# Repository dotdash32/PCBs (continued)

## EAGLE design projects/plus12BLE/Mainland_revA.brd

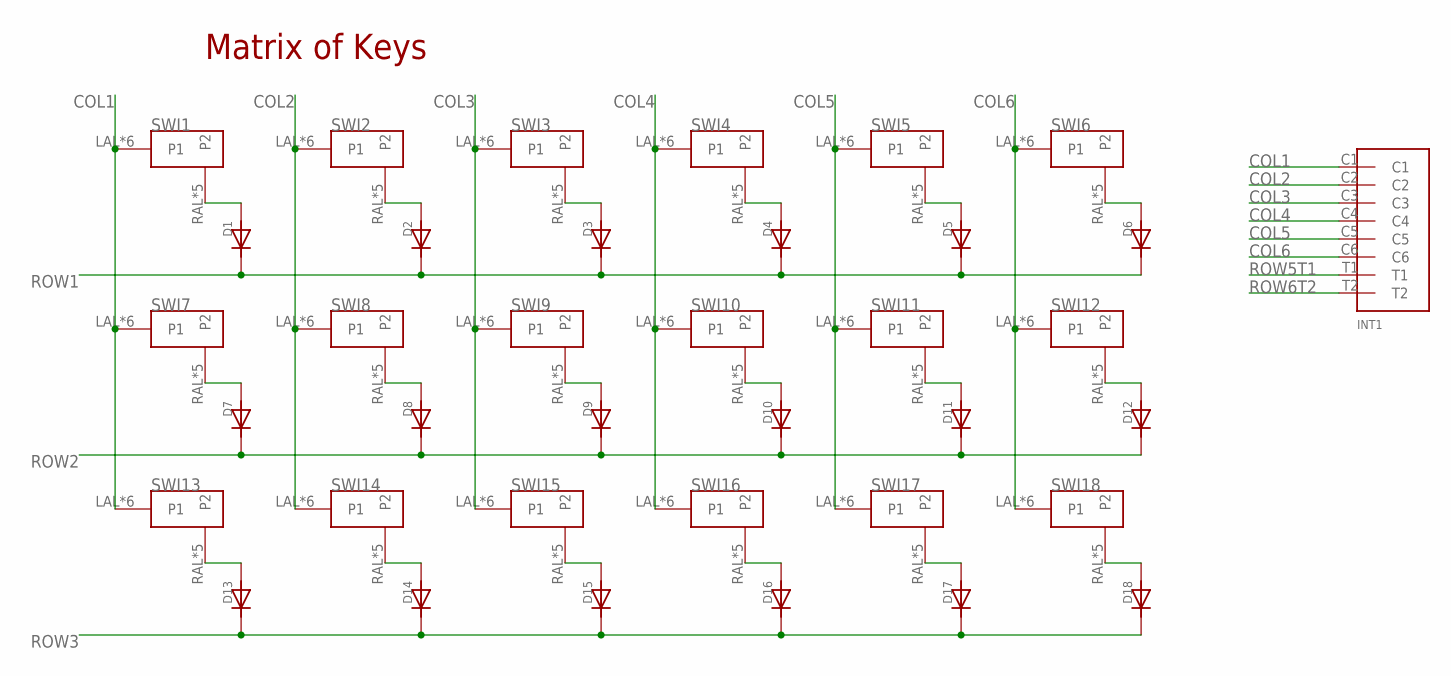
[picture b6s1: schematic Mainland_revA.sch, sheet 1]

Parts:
D1, D2, D3, D4, D5, D6, D7, D8, D9, D10, D11, D12, D13, D14, D15, D16, D17, D18: DIODE; DIODE_COMBO
INT1: INTRCNNT4X2; INTRRIBBON
SWI1, SWI2, SWI3, SWI4, SWI5, SWI6, SWI7, SWI8, SWI9, SWI10, SWI11, SWI12, SWI13, SWI14, SWI15, SWI16, SWI17, SWI18: MX/ALPSDOUBLESIDED; DOUBLED_MX/ALPS

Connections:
COL1: INT1.C1, SWI1.LAL (P1), SWI1.LAR (P1), SWI1.LCL (P1), SWI1.LCR (P1), SWI1.LLP (P1), SWI1.LRLP (P1), SWI7.LAL (P1), SWI7.LAR (P1), SWI7.LCL (P1), SWI7.LCR (P1), SWI7.LLP (P1), SWI7.LRLP (P1), SWI13.LAL (P1), SWI13.LAR (P1), SWI13.LCL (P1), SWI13.LCR (P1), SWI13.LLP (P1), SWI13.LRLP (P1); also elsewhere on the board
COL2: INT1.C2, SWI2.LAL (P1), SWI2.LAR (P1), SWI2.LCL (P1), SWI2.LCR (P1), SWI2.LLP (P1), SWI2.LRLP (P1), SWI8.LAL (P1), SWI8.LAR (P1), SWI8.LCL (P1), SWI8.LCR (P1), SWI8.LLP (P1), SWI8.LRLP (P1), SWI14.LAL (P1), SWI14.LAR (P1), SWI14.LCL (P1), SWI14.LCR (P1), SWI14.LLP (P1), SWI14.LRLP (P1); also elsewhere on the board
COL3: INT1.C3, SWI3.LAL (P1), SWI3.LAR (P1), SWI3.LCL (P1), SWI3.LCR (P1), SWI3.LLP (P1), SWI3.LRLP (P1), SWI9.LAL (P1), SWI9.LAR (P1), SWI9.LCL (P1), SWI9.LCR (P1), SWI9.LLP (P1), SWI9.LRLP (P1), SWI15.LAL (P1), SWI15.LAR (P1), SWI15.LCL (P1), SWI15.LCR (P1), SWI15.LLP (P1), SWI15.LRLP (P1); also elsewhere on the board
COL4: INT1.C4, SWI4.LAL (P1), SWI4.LAR (P1), SWI4.LCL (P1), SWI4.LCR (P1), SWI4.LLP (P1), SWI4.LRLP (P1), SWI10.LAL (P1), SWI10.LAR (P1), SWI10.LCL (P1), SWI10.LCR (P1), SWI10.LLP (P1), SWI10.LRLP (P1), SWI16.LAL (P1), SWI16.LAR (P1), SWI16.LCL (P1), SWI16.LCR (P1), SWI16.LLP (P1), SWI16.LRLP (P1); also elsewhere on the board
COL5: INT1.C5, SWI5.LAL (P1), SWI5.LAR (P1), SWI5.LCL (P1), SWI5.LCR (P1), SWI5.LLP (P1), SWI5.LRLP (P1), SWI11.LAL (P1), SWI11.LAR (P1), SWI11.LCL (P1), SWI11.LCR (P1), SWI11.LLP (P1), SWI11.LRLP (P1), SWI17.LAL (P1), SWI17.LAR (P1), SWI17.LCL (P1), SWI17.LCR (P1), SWI17.LLP (P1), SWI17.LRLP (P1); also elsewhere on the board
COL6: INT1.C6, SWI6.LAL (P1), SWI6.LAR (P1), SWI6.LCL (P1), SWI6.LCR (P1), SWI6.LLP (P1), SWI6.LRLP (P1), SWI12.LAL (P1), SWI12.LAR (P1), SWI12.LCL (P1), SWI12.LCR (P1), SWI12.LLP (P1), SWI12.LRLP (P1), SWI18.LAL (P1), SWI18.LAR (P1), SWI18.LCL (P1), SWI18.LCR (P1), SWI18.LLP (P1), SWI18.LRLP (P1); also elsewhere on the board
unnamed: D1.ANOSB (AN), D1.ANOST (AN), D1.ANOT (AN), SWI1.RAL (P2), SWI1.RAR (P2), SWI1.RCL (P2), SWI1.RCR (P2), SWI1.RLMID (P2)
unnamed: D2.ANOSB (AN), D2.ANOST (AN), D2.ANOT (AN), SWI2.RAL (P2), SWI2.RAR (P2), SWI2.RCL (P2), SWI2.RCR (P2), SWI2.RLMID (P2)
unnamed: D3.ANOSB (AN), D3.ANOST (AN), D3.ANOT (AN), SWI3.RAL (P2), SWI3.RAR (P2), SWI3.RCL (P2), SWI3.RCR (P2), SWI3.RLMID (P2)
unnamed: D4.ANOSB (AN), D4.ANOST (AN), D4.ANOT (AN), SWI4.RAL (P2), SWI4.RAR (P2), SWI4.RCL (P2), SWI4.RCR (P2), SWI4.RLMID (P2)
unnamed: D5.ANOSB (AN), D5.ANOST (AN), D5.ANOT (AN), SWI5.RAL (P2), SWI5.RAR (P2), SWI5.RCL (P2), SWI5.RCR (P2), SWI5.RLMID (P2)
unnamed: D6.ANOSB (AN), D6.ANOST (AN), D6.ANOT (AN), SWI6.RAL (P2), SWI6.RAR (P2), SWI6.RCL (P2), SWI6.RCR (P2), SWI6.RLMID (P2)
unnamed: D7.ANOSB (AN), D7.ANOST (AN), D7.ANOT (AN), SWI7.RAL (P2), SWI7.RAR (P2), SWI7.RCL (P2), SWI7.RCR (P2), SWI7.RLMID (P2)
unnamed: D8.ANOSB (AN), D8.ANOST (AN), D8.ANOT (AN), SWI8.RAL (P2), SWI8.RAR (P2), SWI8.RCL (P2), SWI8.RCR (P2), SWI8.RLMID (P2)
unnamed: D9.ANOSB (AN), D9.ANOST (AN), D9.ANOT (AN), SWI9.RAL (P2), SWI9.RAR (P2), SWI9.RCL (P2), SWI9.RCR (P2), SWI9.RLMID (P2)
unnamed: D10.ANOSB (AN), D10.ANOST (AN), D10.ANOT (AN), SWI10.RAL (P2), SWI10.RAR (P2), SWI10.RCL (P2), SWI10.RCR (P2), SWI10.RLMID (P2)
unnamed: D11.ANOSB (AN), D11.ANOST (AN), D11.ANOT (AN), SWI11.RAL (P2), SWI11.RAR (P2), SWI11.RCL (P2), SWI11.RCR (P2), SWI11.RLMID (P2)
unnamed: D12.ANOSB (AN), D12.ANOST (AN), D12.ANOT (AN), SWI12.RAL (P2), SWI12.RAR (P2), SWI12.RCL (P2), SWI12.RCR (P2), SWI12.RLMID (P2)
unnamed: D13.ANOSB (AN), D13.ANOST (AN), D13.ANOT (AN), SWI13.RAL (P2), SWI13.RAR (P2), SWI13.RCL (P2), SWI13.RCR (P2), SWI13.RLMID (P2)
unnamed: D14.ANOSB (AN), D14.ANOST (AN), D14.ANOT (AN), SWI14.RAL (P2), SWI14.RAR (P2), SWI14.RCL (P2), SWI14.RCR (P2), SWI14.RLMID (P2)
unnamed: D15.ANOSB (AN), D15.ANOST (AN), D15.ANOT (AN), SWI15.RAL (P2), SWI15.RAR (P2), SWI15.RCL (P2), SWI15.RCR (P2), SWI15.RLMID (P2)
unnamed: D16.ANOSB (AN), D16.ANOST (AN), D16.ANOT (AN), SWI16.RAL (P2), SWI16.RAR (P2), SWI16.RCL (P2), SWI16.RCR (P2), SWI16.RLMID (P2)
unnamed: D17.ANOSB (AN), D17.ANOST (AN), D17.ANOT (AN), SWI17.RAL (P2), SWI17.RAR (P2), SWI17.RCL (P2), SWI17.RCR (P2), SWI17.RLMID (P2)
unnamed: D18.ANOSB (AN), D18.ANOST (AN), D18.ANOT (AN), SWI18.RAL (P2), SWI18.RAR (P2), SWI18.RCL (P2), SWI18.RCR (P2), SWI18.RLMID (P2)
ROW1: D1.CATSB (CAT), D1.CATST (CAT), D1.CATT (CAT), D2.CATSB (CAT), D2.CATST (CAT), D2.CATT (CAT), D3.CATSB (CAT), D3.CATST (CAT), D3.CATT (CAT), D4.CATSB (CAT), D4.CATST (CAT), D4.CATT (CAT), D5.CATSB (CAT), D5.CATST (CAT), D5.CATT (CAT), D6.CATSB (CAT), D6.CATST (CAT), D6.CATT (CAT); also elsewhere on the board
ROW2: D7.CATSB (CAT), D7.CATST (CAT), D7.CATT (CAT), D8.CATSB (CAT), D8.CATST (CAT), D8.CATT (CAT), D9.CATSB (CAT), D9.CATST (CAT), D9.CATT (CAT), D10.CATSB (CAT), D10.CATST (CAT), D10.CATT (CAT), D11.CATSB (CAT), D11.CATST (CAT), D11.CATT (CAT), D12.CATSB (CAT), D12.CATST (CAT), D12.CATT (CAT); also elsewhere on the board
ROW3: D13.CATSB (CAT), D13.CATST (CAT), D13.CATT (CAT), D14.CATSB (CAT), D14.CATST (CAT), D14.CATT (CAT), D15.CATSB (CAT), D15.CATST (CAT), D15.CATT (CAT), D16.CATSB (CAT), D16.CATST (CAT), D16.CATT (CAT), D17.CATSB (CAT), D17.CATST (CAT), D17.CATT (CAT), D18.CATSB (CAT), D18.CATST (CAT), D18.CATT (CAT); also elsewhere on the board
ROW5T1: INT1.T1; also elsewhere on the board
ROW6T2: INT1.T2; also elsewhere on the board

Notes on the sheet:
Matrix of Keys

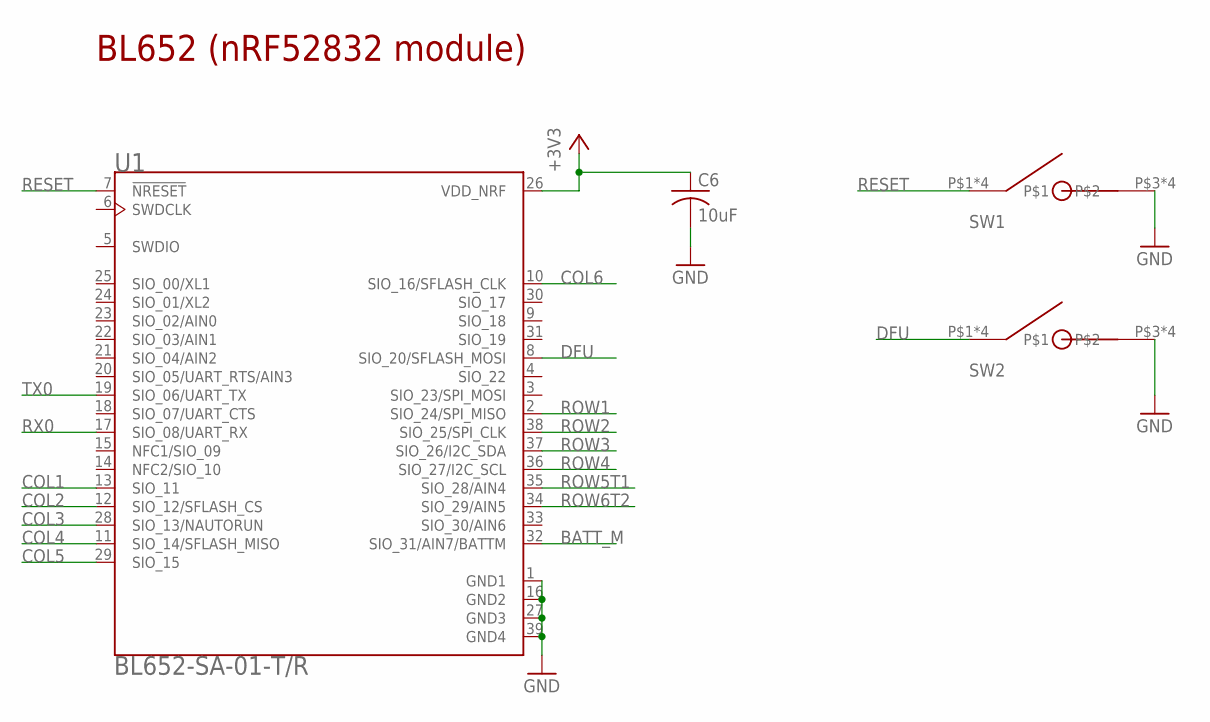
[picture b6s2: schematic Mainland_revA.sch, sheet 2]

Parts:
C6: 10uF; C0805K
SW1, SW2: RSTSWSMD; FLATSWT
U1: BL652-SA-01-T/R; XCVR_BL652-SA-01-T/R

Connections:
+3V3: C6.1, U1.26 (VDD_NRF); also elsewhere on the board
BATT_M: U1.32 (SIO_31/AIN7/BATTM); also elsewhere on the board
COL1: U1.13 (SIO_11); also elsewhere on the board
COL2: U1.12 (SIO_12/SFLASH_CS); also elsewhere on the board
COL3: U1.28 (SIO_13/NAUTORUN); also elsewhere on the board
COL4: U1.11 (SIO_14/SFLASH_MISO); also elsewhere on the board
COL5: U1.29 (SIO_15); also elsewhere on the board
COL6: U1.10 (SIO_16/SFLASH_CLK); also elsewhere on the board
DFU: SW2.P$1, SW2.P$2, SW2.P$5, SW2.P$6, U1.8 (SIO_20/SFLASH_MOSI)
GND: C6.2, SW1.P$3, SW1.P$4, SW1.P$7, SW1.P$8, SW2.P$3, SW2.P$4, SW2.P$7, SW2.P$8, U1.1 (GND1), U1.16 (GND2), U1.27 (GND3), U1.39 (GND4); also elsewhere on the board
RESET: SW1.P$1, SW1.P$2, SW1.P$5, SW1.P$6, U1.7 (!NRESET)
ROW1: U1.2 (SIO_24/SPI_MISO); also elsewhere on the board
ROW2: U1.38 (SIO_25/SPI_CLK); also elsewhere on the board
ROW3: U1.37 (SIO_26/I2C_SDA); also elsewhere on the board
ROW4: U1.36 (SIO_27/I2C_SCL)
ROW5T1: U1.35 (SIO_28/AIN4); also elsewhere on the board
ROW6T2: U1.34 (SIO_29/AIN5); also elsewhere on the board
RX0: U1.17 (SIO_08/UART_RX); also elsewhere on the board
TX0: U1.19 (SIO_06/UART_TX); also elsewhere on the board

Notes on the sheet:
BL652 (nRF52832 module)

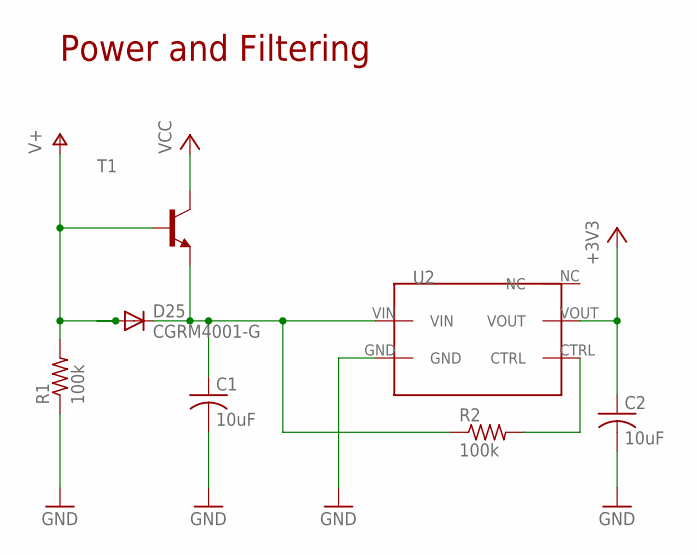
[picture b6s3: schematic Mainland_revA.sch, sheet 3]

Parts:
C1, C2: 10uF; C0805K
D25: CGRM4001-G; SOD-123_MINI-SMA
R1, R2: 100k; R0402
T1: BC808-NPN-SOT23-BEC; SOT23-BEC
U2: TCR2EF

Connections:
+3V3: C2.1, U2.VOUT; also elsewhere on the board
GND: C1.2, C2.2, R1.1, U2.GND; also elsewhere on the board
unnamed: R2.2, U2.CTRL
unnamed: C1.1, D25.C, R2.1, T1.E, U2.VIN
V+: D25.A, R1.2, T1.B; also elsewhere on the board
VCC: T1.C; also elsewhere on the board

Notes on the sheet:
Power and Filtering

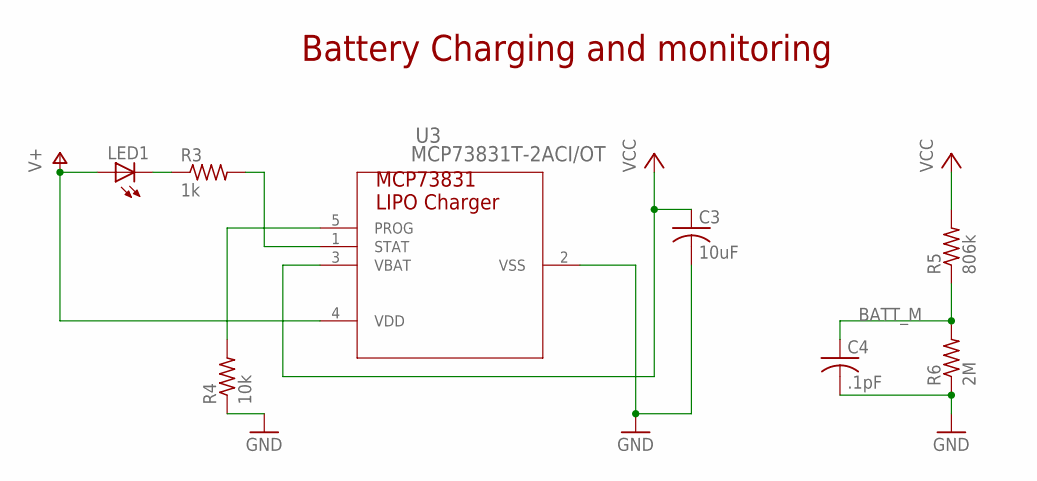
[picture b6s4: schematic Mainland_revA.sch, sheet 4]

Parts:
C3: 10uF; C0805K
C4: .1pF; C0402K
LED1: LEDCHIP-LED0603; CHIP-LED0603
R3: 1k; R0402
R4: 10k; R0402
R5: 806k; R0402
R6: 2M; R0402
U3: MCP73831T-2ACI/OT; SOT-23-5_MC

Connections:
BATT_M: C4.1, R5.1, R6.2; also elsewhere on the board
GND: C3.2, C4.2, R4.1, R6.1, U3.2 (VSS); also elsewhere on the board
unnamed: LED1.C, R3.1
unnamed: R3.2, U3.1 (STAT)
unnamed: R4.2, U3.5 (PROG)
V+: LED1.A, U3.4 (VDD); also elsewhere on the board
VCC: C3.1, R5.2, U3.3 (VBAT); also elsewhere on the board

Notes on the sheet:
Battery Charging and monitoring

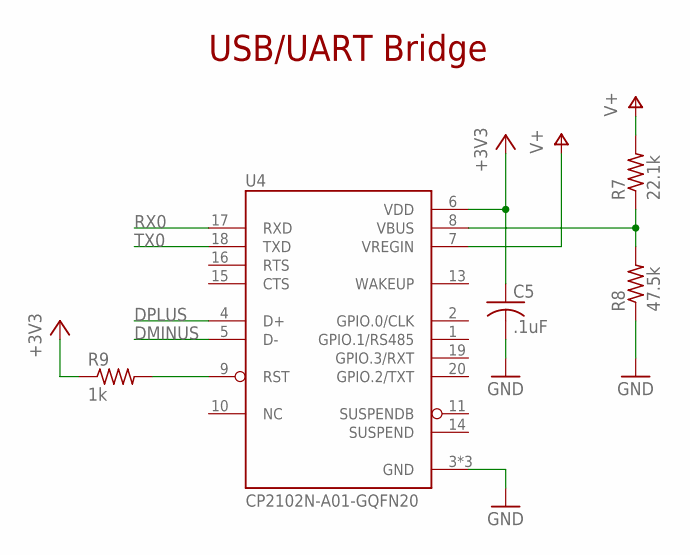
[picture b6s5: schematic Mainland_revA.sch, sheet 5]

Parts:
C5: .1uF; C0402K
R7: 22.1k; R0402
R8: 47.5k; R0402
R9: 1k; R0402
U4: CP2102N-A01-GQFN20; SILABS_QFN20

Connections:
+3V3: C5.1, R9.1, U4.6 (VDD); also elsewhere on the board
DMINUS: U4.5 (D-); also elsewhere on the board
DPLUS: U4.4 (D+); also elsewhere on the board
GND: C5.2, R8.1, U4.3 (GND), U4.12 (GND), U4.21 (GND); also elsewhere on the board
unnamed: R7.1, R8.2, U4.8 (VBUS)
unnamed: R9.2, U4.9 (RST)
RX0: U4.17 (RXD); also elsewhere on the board
TX0: U4.18 (TXD); also elsewhere on the board
V+: R7.2, U4.7 (VREGIN); also elsewhere on the board

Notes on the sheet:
USB/UART Bridge

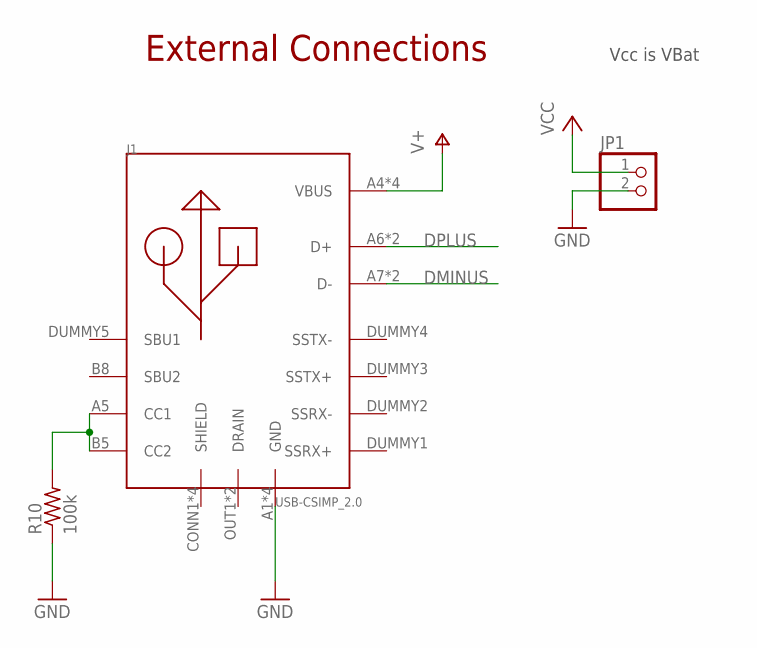
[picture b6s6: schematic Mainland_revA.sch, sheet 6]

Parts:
J1: USB-CSIMP_2.0; CX70M-P1_SIMP
JP1: PINHD-1X2; 1X02
R10: 100k; R0402

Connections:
DMINUS: J1.A7 (D-), J1.B7 (D-); also elsewhere on the board
DPLUS: J1.A6 (D+), J1.B6 (D+); also elsewhere on the board
GND: J1.A1 (GND), J1.A12 (GND), J1.B1 (GND), J1.B12 (GND), JP1.2, R10.1; also elsewhere on the board
unnamed: J1.A5 (CC1), J1.B5 (CC2), R10.2
V+: J1.A4 (VBUS), J1.A9 (VBUS), J1.B4 (VBUS), J1.B9 (VBUS); also elsewhere on the board
VCC: JP1.1; also elsewhere on the board

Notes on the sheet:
External Connections
Vcc is VBat

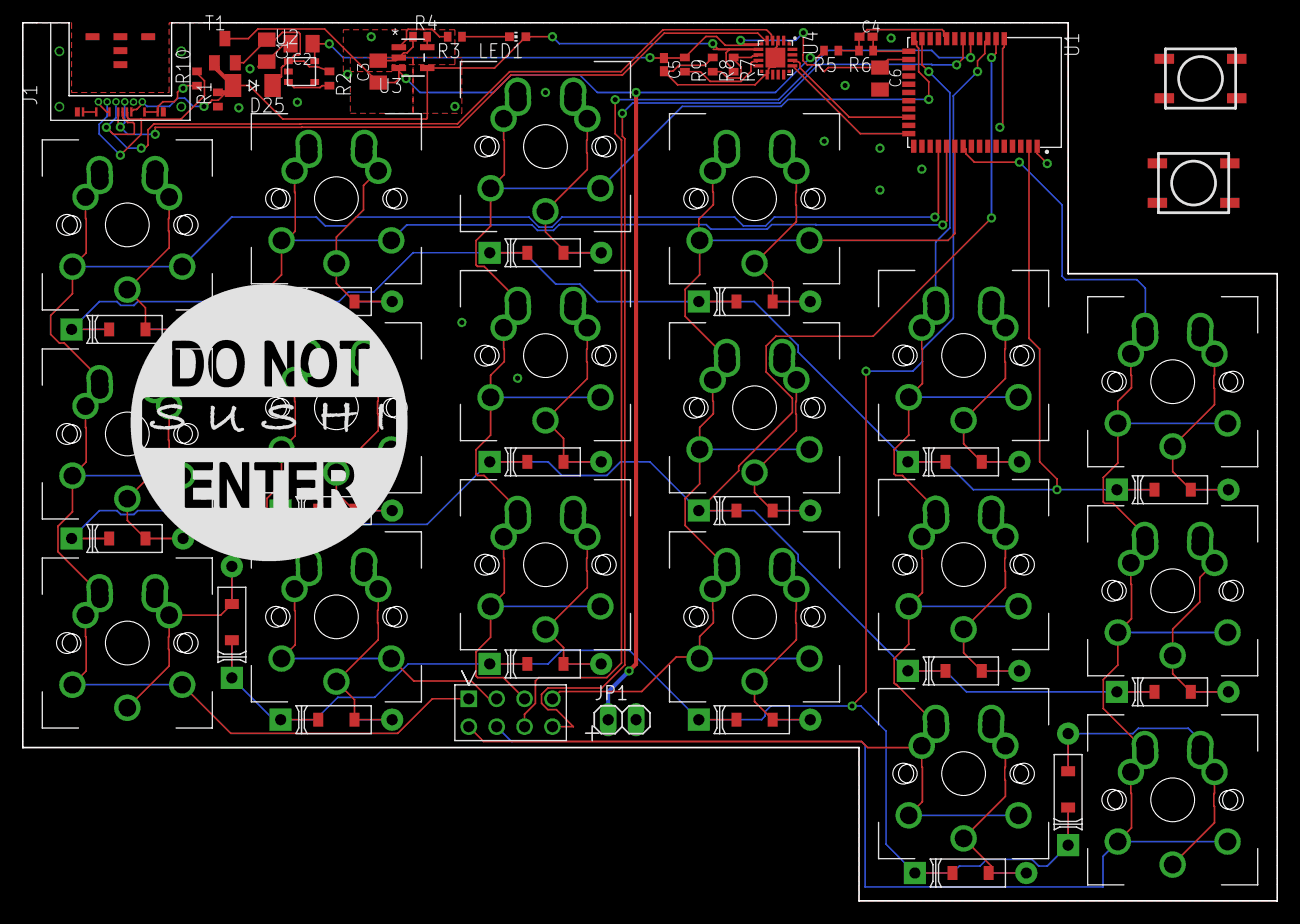
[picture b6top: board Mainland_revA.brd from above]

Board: 2 copper layers, 114.3 x 80.0 mm, 66 parts (0 on the bottom side), 48 nets.

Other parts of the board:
U$1: 1INCH_TOP
U$2: 1INCH_BOT

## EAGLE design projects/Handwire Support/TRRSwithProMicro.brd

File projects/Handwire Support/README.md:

# Handwire Support

A small, simple PCB to help with handwiring. 
Made for a gift keyboard, because I needed the TRRS jack to be mounted, and thought:
"why not put the PM on there too, to keep it even simpler?"

Thus this project was born. 
I'm using the Othermill's default 1/32 inch Design Rules, because it lets me cut fast. 
It's designed so that it fits on the outside edge over the pinky keys.
Optimally, it works well with a very extreme pinky stagger, but otherwise it just sits a little higher.

The board is designed as reversible, so it will flip between sides of the board.
It can be made on one sided FR1, all the connections are routed on both sides.

This is very much a stopgap measure so I can prototype faster, it won't likely make it to GB.  
For something that does this, but better, I believe Key+ project has a dedicated controller.

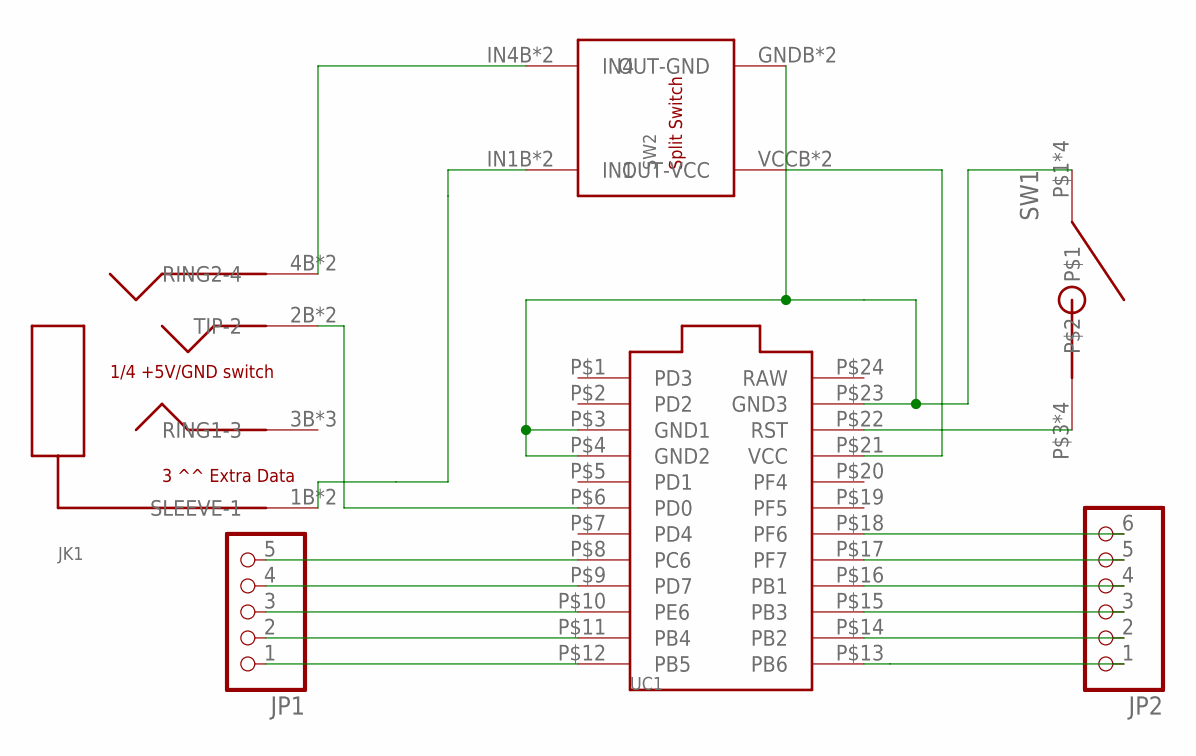
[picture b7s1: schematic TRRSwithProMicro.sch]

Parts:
JK1: TRRSJACKOVER; TRRSJACK_OVER
JP1: PINHD-1X5; 1X05
JP2: PINHD-1X6; 1X06
SW1: RSTSWSMD; FLATSWT
SW2: TRANSFERPADDY; TRANSFER_PADS
UC1: PROMICROTOP; PROMICRO

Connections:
unnamed: JK1.1B (SLEEVE-1), JK1.1T (SLEEVE-1), SW2.IN1B (IN1), SW2.IN1T (IN1)
unnamed: SW1.P$1, SW1.P$2, SW1.P$5, SW1.P$6, SW2.GNDB (OUT-GND), SW2.GNDT (OUT-GND), UC1.P$3 (GND1), UC1.P$4 (GND2), UC1.P$23 (GND3)
unnamed: JK1.2B (TIP-2), JK1.2T (TIP-2), UC1.P$6 (PD0)
unnamed: JK1.4B (RING2-4), JK1.4T (RING2-4), SW2.IN4B (IN4), SW2.IN4T (IN4)
unnamed: SW1.P$3, SW1.P$4, SW1.P$7, SW1.P$8, UC1.P$22 (RST)
unnamed: JP1.1, UC1.P$12 (PB5)
unnamed: JP1.2, UC1.P$11 (PB4)
unnamed: JP1.3, UC1.P$10 (PE6)
unnamed: JP1.4, UC1.P$9 (PD7)
unnamed: JP2.1, UC1.P$13 (PB6)
unnamed: JP2.2, UC1.P$14 (PB2)
unnamed: JP2.3, UC1.P$15 (PB3)
unnamed: JP2.4, UC1.P$16 (PB1)
unnamed: JP2.5, UC1.P$17 (PF7)
unnamed: JP2.6, UC1.P$18 (PF6)
unnamed: JP1.5, UC1.P$8 (PC6)
unnamed: SW2.VCCB (OUT-VCC), SW2.VCCT (OUT-VCC), UC1.P$21 (VCC)

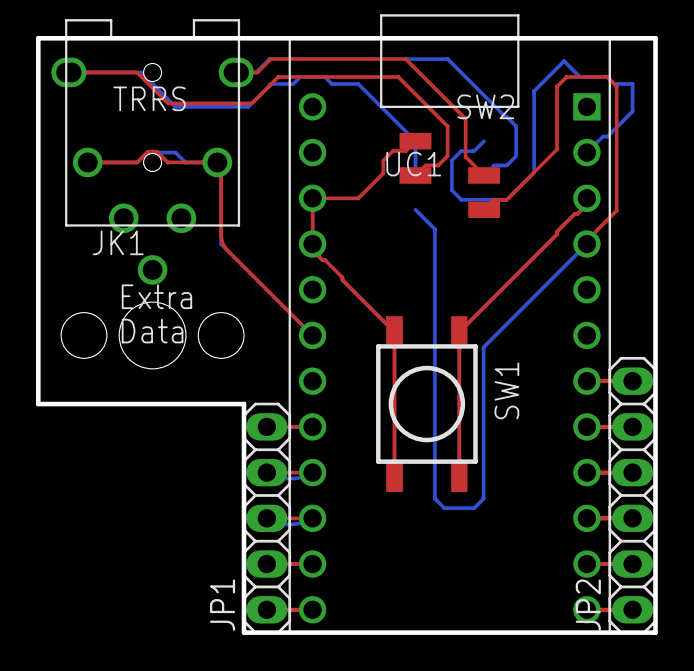
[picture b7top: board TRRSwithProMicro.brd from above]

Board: 2 copper layers, 34.3 x 33.0 mm, 6 parts (0 on the bottom side), 17 nets.

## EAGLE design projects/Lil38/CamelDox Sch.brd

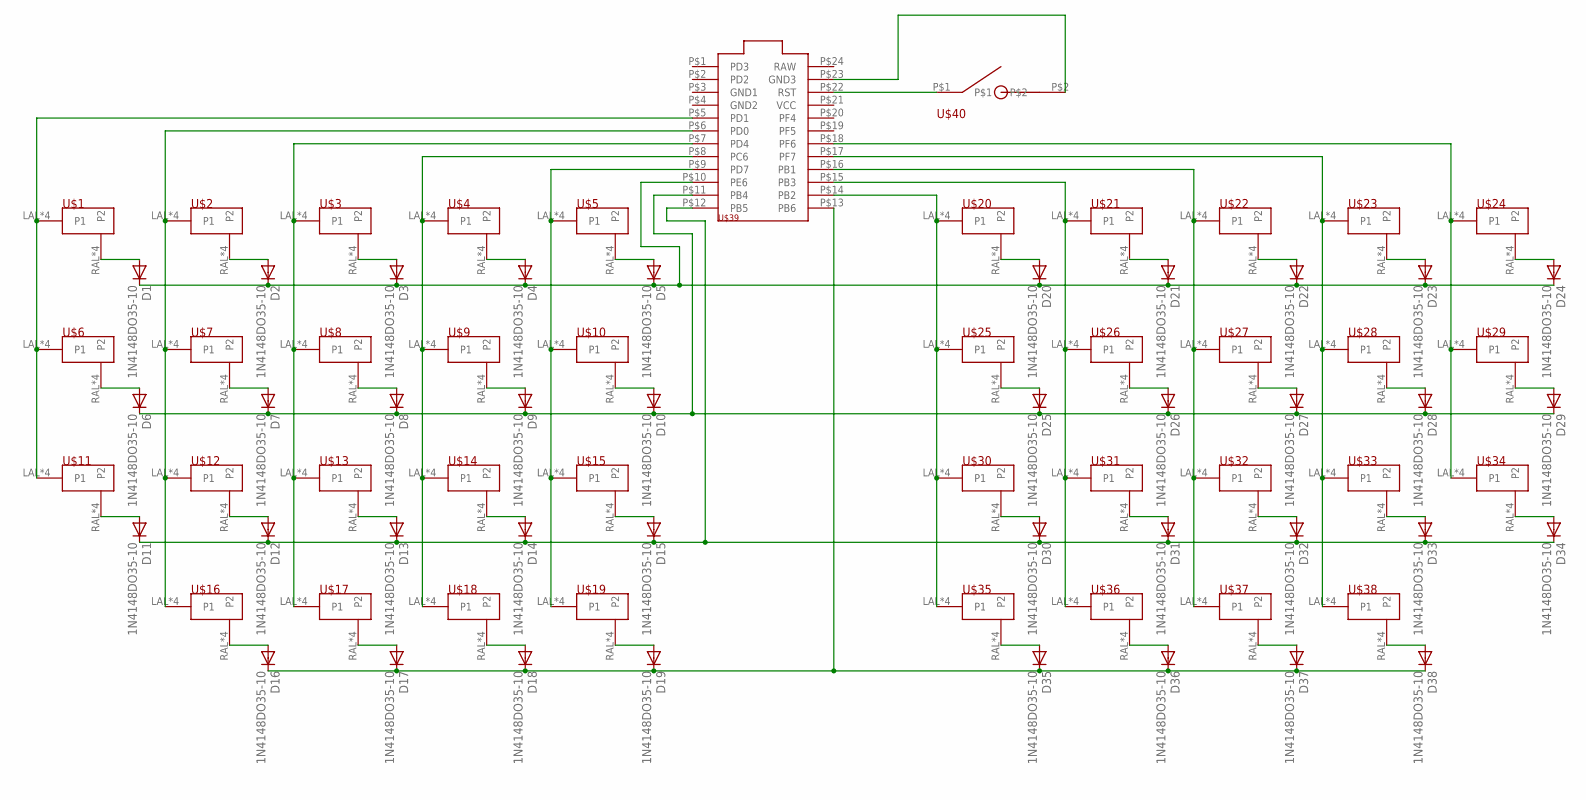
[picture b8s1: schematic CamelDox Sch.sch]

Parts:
D1, D2, D3, D4, D5, D6, D7, D8, D9, D10, D11, D12, D13, D14, D15, D16, D17, D18, D19, D20, D21, D22, D23, D24, D25, D26, D27, D28, D29, D30, D31, D32, D33, D34, D35, D36, D37, D38: 1N4148DO35-10; DO35-10
U$1, U$2, U$3, U$4, U$5, U$6, U$7, U$8, U$9, U$10, U$11, U$12, U$13, U$14, U$15, U$16, U$17, U$18, U$19, U$20, U$21, U$22, U$23, U$24, U$25, U$26, U$27, U$28, U$29, U$30, U$31, U$32, U$33, U$34, U$35, U$36, U$37, U$38: MANDOUBLEONESIDED; MX/ALPS
U$39: PROMICRO
U$40: RSTSW; SKHL

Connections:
unnamed: U$1.LAL (P1), U$1.LAR (P1), U$1.LCL (P1), U$1.LCR (P1), U$6.LAL (P1), U$6.LAR (P1), U$6.LCL (P1), U$6.LCR (P1), U$11.LAL (P1), U$11.LAR (P1), U$11.LCL (P1), U$11.LCR (P1), U$39.P$5 (PD1)
unnamed: D1.A, U$1.RAL (P2), U$1.RAR (P2), U$1.RCL (P2), U$1.RCR (P2)
unnamed: D2.A, U$2.RAL (P2), U$2.RAR (P2), U$2.RCL (P2), U$2.RCR (P2)
unnamed: D3.A, U$3.RAL (P2), U$3.RAR (P2), U$3.RCL (P2), U$3.RCR (P2)
unnamed: D4.A, U$4.RAL (P2), U$4.RAR (P2), U$4.RCL (P2), U$4.RCR (P2)
unnamed: D5.A, U$5.RAL (P2), U$5.RAR (P2), U$5.RCL (P2), U$5.RCR (P2)
unnamed: D6.A, U$6.RAL (P2), U$6.RAR (P2), U$6.RCL (P2), U$6.RCR (P2)
unnamed: D7.A, U$7.RAL (P2), U$7.RAR (P2), U$7.RCL (P2), U$7.RCR (P2)
unnamed: D8.A, U$8.RAL (P2), U$8.RAR (P2), U$8.RCL (P2), U$8.RCR (P2)
unnamed: D9.A, U$9.RAL (P2), U$9.RAR (P2), U$9.RCL (P2), U$9.RCR (P2)
unnamed: D10.A, U$10.RAL (P2), U$10.RAR (P2), U$10.RCL (P2), U$10.RCR (P2)
unnamed: D11.A, U$11.RAL (P2), U$11.RAR (P2), U$11.RCL (P2), U$11.RCR (P2)
unnamed: D12.A, U$12.RAL (P2), U$12.RAR (P2), U$12.RCL (P2), U$12.RCR (P2)
unnamed: D13.A, U$13.RAL (P2), U$13.RAR (P2), U$13.RCL (P2), U$13.RCR (P2)
unnamed: D14.A, U$14.RAL (P2), U$14.RAR (P2), U$14.RCL (P2), U$14.RCR (P2)
unnamed: D15.A, U$15.RAL (P2), U$15.RAR (P2), U$15.RCL (P2), U$15.RCR (P2)
unnamed: D16.A, U$16.RAL (P2), U$16.RAR (P2), U$16.RCL (P2), U$16.RCR (P2)
unnamed: D17.A, U$17.RAL (P2), U$17.RAR (P2), U$17.RCL (P2), U$17.RCR (P2)
unnamed: D18.A, U$18.RAL (P2), U$18.RAR (P2), U$18.RCL (P2), U$18.RCR (P2)
unnamed: D19.A, U$19.RAL (P2), U$19.RAR (P2), U$19.RCL (P2), U$19.RCR (P2)
unnamed: U$2.LAL (P1), U$2.LAR (P1), U$2.LCL (P1), U$2.LCR (P1), U$7.LAL (P1), U$7.LAR (P1), U$7.LCL (P1), U$7.LCR (P1), U$12.LAL (P1), U$12.LAR (P1), U$12.LCL (P1), U$12.LCR (P1), U$16.LAL (P1), U$16.LAR (P1), U$16.LCL (P1), U$16.LCR (P1), U$39.P$6 (PD0)
unnamed: U$3.LAL (P1), U$3.LAR (P1), U$3.LCL (P1), U$3.LCR (P1), U$8.LAL (P1), U$8.LAR (P1), U$8.LCL (P1), U$8.LCR (P1), U$13.LAL (P1), U$13.LAR (P1), U$13.LCL (P1), U$13.LCR (P1), U$17.LAL (P1), U$17.LAR (P1), U$17.LCL (P1), U$17.LCR (P1), U$39.P$7 (PD4)
unnamed: U$4.LAL (P1), U$4.LAR (P1), U$4.LCL (P1), U$4.LCR (P1), U$9.LAL (P1), U$9.LAR (P1), U$9.LCL (P1), U$9.LCR (P1), U$14.LAL (P1), U$14.LAR (P1), U$14.LCL (P1), U$14.LCR (P1), U$18.LAL (P1), U$18.LAR (P1), U$18.LCL (P1), U$18.LCR (P1), U$39.P$8 (PC6)
unnamed: U$5.LAL (P1), U$5.LAR (P1), U$5.LCL (P1), U$5.LCR (P1), U$10.LAL (P1), U$10.LAR (P1), U$10.LCL (P1), U$10.LCR (P1), U$15.LAL (P1), U$15.LAR (P1), U$15.LCL (P1), U$15.LCR (P1), U$19.LAL (P1), U$19.LAR (P1), U$19.LCL (P1), U$19.LCR (P1), U$39.P$9 (PD7)
unnamed: D1.C, D2.C, D3.C, D4.C, D5.C, D20.C, D21.C, D22.C, D23.C, D24.C, U$39.P$10 (PE6)
unnamed: D6.C, D7.C, D8.C, D9.C, D10.C, D25.C, D26.C, D27.C, D28.C, D29.C, U$39.P$11 (PB4)
unnamed: D11.C, D12.C, D13.C, D14.C, D15.C, D30.C, D31.C, D32.C, D33.C, D34.C, U$39.P$12 (PB5)
unnamed: D16.C, D17.C, D18.C, D19.C, D35.C, D36.C, D37.C, D38.C, U$39.P$13 (PB6)
unnamed: U$20.LAL (P1), U$20.LAR (P1), U$20.LCL (P1), U$20.LCR (P1), U$25.LAL (P1), U$25.LAR (P1), U$25.LCL (P1), U$25.LCR (P1), U$30.LAL (P1), U$30.LAR (P1), U$30.LCL (P1), U$30.LCR (P1), U$35.LAL (P1), U$35.LAR (P1), U$35.LCL (P1), U$35.LCR (P1), U$39.P$14 (PB2)
unnamed: D20.A, U$20.RAL (P2), U$20.RAR (P2), U$20.RCL (P2), U$20.RCR (P2)
unnamed: D21.A, U$21.RAL (P2), U$21.RAR (P2), U$21.RCL (P2), U$21.RCR (P2)
unnamed: D22.A, U$22.RAL (P2), U$22.RAR (P2), U$22.RCL (P2), U$22.RCR (P2)
unnamed: D23.A, U$23.RAL (P2), U$23.RAR (P2), U$23.RCL (P2), U$23.RCR (P2)
unnamed: D24.A, U$24.RAL (P2), U$24.RAR (P2), U$24.RCL (P2), U$24.RCR (P2)
unnamed: D25.A, U$25.RAL (P2), U$25.RAR (P2), U$25.RCL (P2), U$25.RCR (P2)
unnamed: D26.A, U$26.RAL (P2), U$26.RAR (P2), U$26.RCL (P2), U$26.RCR (P2)
unnamed: D27.A, U$27.RAL (P2), U$27.RAR (P2), U$27.RCL (P2), U$27.RCR (P2)
unnamed: D28.A, U$28.RAL (P2), U$28.RAR (P2), U$28.RCL (P2), U$28.RCR (P2)
unnamed: D29.A, U$29.RAL (P2), U$29.RAR (P2), U$29.RCL (P2), U$29.RCR (P2)
unnamed: D30.A, U$30.RAL (P2), U$30.RAR (P2), U$30.RCL (P2), U$30.RCR (P2)
unnamed: D31.A, U$31.RAL (P2), U$31.RAR (P2), U$31.RCL (P2), U$31.RCR (P2)
unnamed: D32.A, U$32.RAL (P2), U$32.RAR (P2), U$32.RCL (P2), U$32.RCR (P2)
unnamed: D33.A, U$33.RAL (P2), U$33.RAR (P2), U$33.RCL (P2), U$33.RCR (P2)
unnamed: D34.A, U$34.RAL (P2), U$34.RAR (P2), U$34.RCL (P2), U$34.RCR (P2)
unnamed: D35.A, U$35.RAL (P2), U$35.RAR (P2), U$35.RCL (P2), U$35.RCR (P2)
unnamed: D36.A, U$36.RAL (P2), U$36.RAR (P2), U$36.RCL (P2), U$36.RCR (P2)
unnamed: D37.A, U$37.RAL (P2), U$37.RAR (P2), U$37.RCL (P2), U$37.RCR (P2)
unnamed: D38.A, U$38.RAL (P2), U$38.RAR (P2), U$38.RCL (P2), U$38.RCR (P2)
unnamed: U$21.LAL (P1), U$21.LAR (P1), U$21.LCL (P1), U$21.LCR (P1), U$26.LAL (P1), U$26.LAR (P1), U$26.LCL (P1), U$26.LCR (P1), U$31.LAL (P1), U$31.LAR (P1), U$31.LCL (P1), U$31.LCR (P1), U$36.LAL (P1), U$36.LAR (P1), U$36.LCL (P1), U$36.LCR (P1), U$39.P$15 (PB3)
unnamed: U$22.LAL (P1), U$22.LAR (P1), U$22.LCL (P1), U$22.LCR (P1), U$27.LAL (P1), U$27.LAR (P1), U$27.LCL (P1), U$27.LCR (P1), U$32.LAL (P1), U$32.LAR (P1), U$32.LCL (P1), U$32.LCR (P1), U$37.LAL (P1), U$37.LAR (P1), U$37.LCL (P1), U$37.LCR (P1), U$39.P$16 (PB1)
unnamed: U$23.LAL (P1), U$23.LAR (P1), U$23.LCL (P1), U$23.LCR (P1), U$28.LAL (P1), U$28.LAR (P1), U$28.LCL (P1), U$28.LCR (P1), U$33.LAL (P1), U$33.LAR (P1), U$33.LCL (P1), U$33.LCR (P1), U$38.LAL (P1), U$38.LAR (P1), U$38.LCL (P1), U$38.LCR (P1), U$39.P$17 (PF7)
unnamed: U$24.LAL (P1), U$24.LAR (P1), U$24.LCL (P1), U$24.LCR (P1), U$29.LAL (P1), U$29.LAR (P1), U$29.LCL (P1), U$29.LCR (P1), U$34.LAL (P1), U$34.LAR (P1), U$34.LCL (P1), U$34.LCR (P1), U$39.P$18 (PF6)
unnamed: U$39.P$22 (RST), U$40.P$1
unnamed: U$39.P$23 (GND3), U$40.P$2

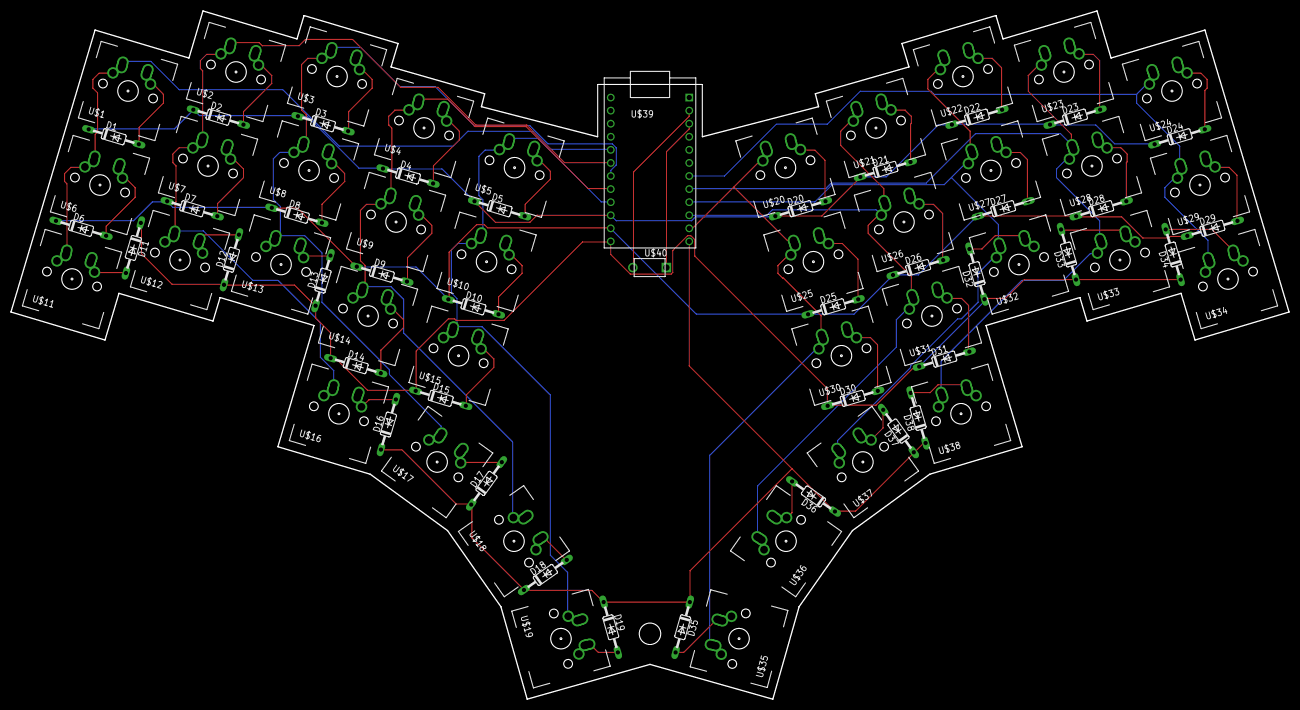
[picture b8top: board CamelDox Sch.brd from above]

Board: 2 copper layers, 248.2 x 133.7 mm, 78 parts (0 on the bottom side), 54 nets.

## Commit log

2018-06-18 re-initializing
2018-06-18 readme edits
2018-06-19 Adding straight thumbs, using Othermill DRCs
2018-06-19 Moving diode to inline position
2018-06-19 Kobe beefing it up
2018-06-19 removing uneeded folder
2018-06-20 Updating library pad sizes
2018-06-20 restoring gitignore settings
2018-07-02 Updates, BEFORE C5/6 Move
2018-07-02 Eagle moved all the files in an update, rip versions
2018-07-06 Storing DRC templates
2018-07-06 Handwire support device v1
2018-07-06 support, v1 pcb
2018-07-06 Adding 3 thumb option
2018-07-06 Working 1/32 version of handwire support
2018-07-06 Ignoring images
2018-07-06 Cutout for easier wires
2018-07-06 fixing hidden folders
2018-07-06 Fixing hidden folder
2018-07-06 creating readme
2018-07-06 Flipping the sides
2018-07-06 description on flipping
2018-07-06 Reversible handwires
2018-07-11 wires instead of routing for double sidedness
2018-07-11 switching headers
2018-07-11 switching interconnects
2018-07-18 library updates
2018-07-18 Getting ready for pictures
2018-07-18 Adding low profile support
2018-07-18 Adding images
2018-07-18 typos
2018-07-18 Making readme with images
2018-07-18 spacing
2018-07-24 Creating prototyping cam job template
2018-10-25 more updates than should be in one commit, lots of work
2018-11-01 working for DFM, new USB connector test
2018-11-02 adding usb c 2.0 device
2018-11-02 saving before autorouter
2018-11-02 revB of plus12BLE and necessary library changes
2018-11-18 Saving version B, before double diodes
2018-11-18 Early version of schematic drawing
